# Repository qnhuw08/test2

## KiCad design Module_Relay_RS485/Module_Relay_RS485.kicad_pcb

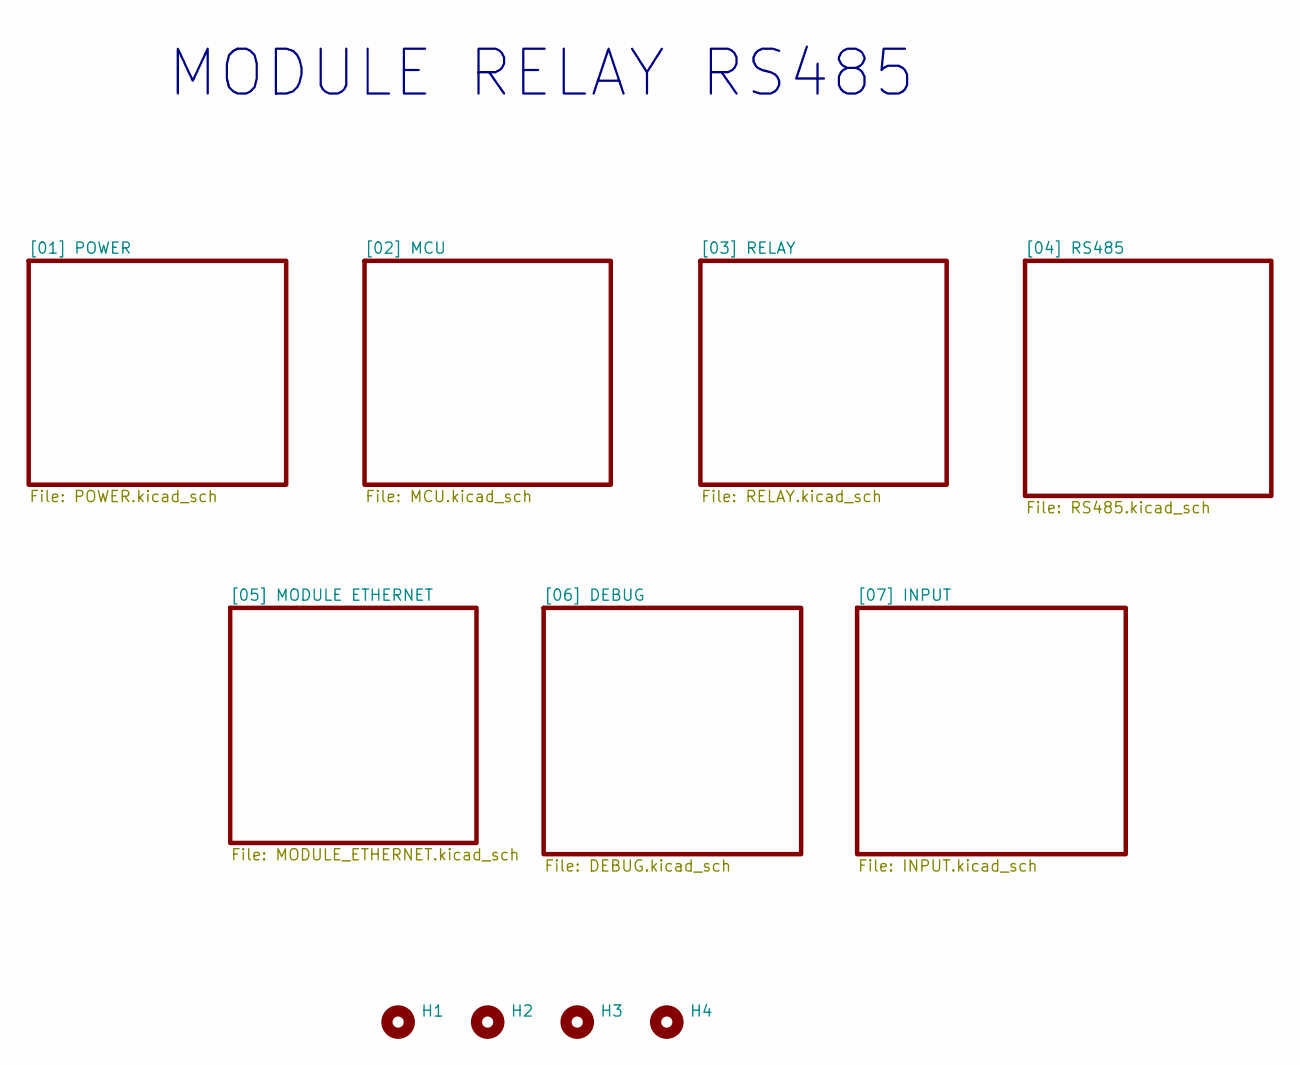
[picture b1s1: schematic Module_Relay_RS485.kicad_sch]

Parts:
H1, H2, H3, H4: MountingHole; MountingHole_3.2mm_M3_DIN965_Pad

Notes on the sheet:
MODULE RELAY RS485

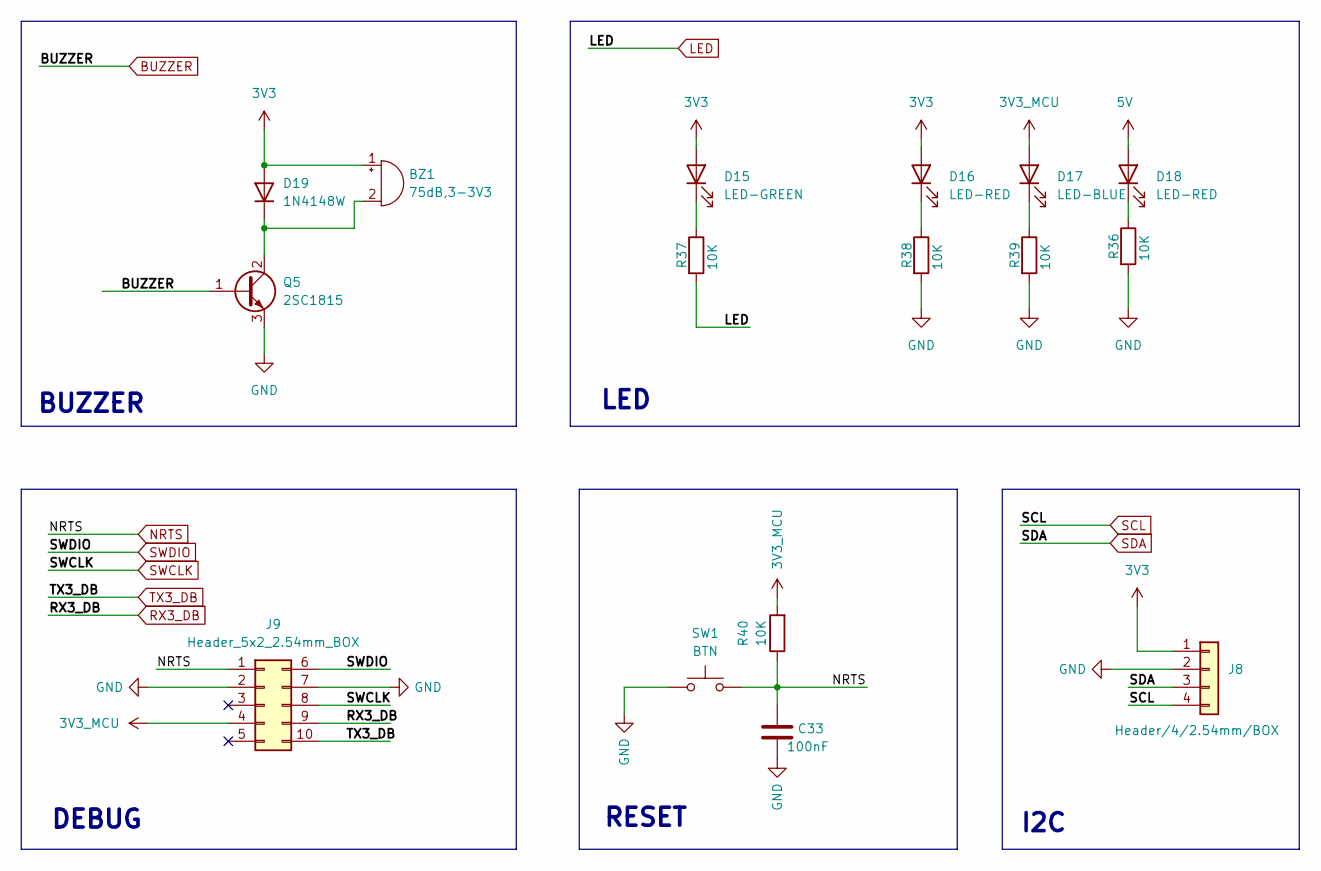
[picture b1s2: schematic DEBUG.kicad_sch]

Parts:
BZ1: 75dB,3-3V3; MagneticBuzzer_PUI_AT-0927-TT-6-R
C33: 100nF; C_0603_1608Metric
D15: LED-GREEN; LED_0805_2012Metric
D16, D18: LED-RED; LED_0805_2012Metric
D17: LED-BLUE; LED_0805_2012Metric
D19: 1N4148W; D_SOD-123
J8: Header/4/2.54mm/BOX; PinHeader_1x04_P2.54mm_Horizontal
J9: Header_5x2_2.54mm_BOX; Header_2x5_2.54mm_BOX
Q5: 2SC1815; SOT-23
R36, R37, R38, R39, R40: 10K; R_0603_1608Metric
SW1: BTN; SW_SPST_PTS645

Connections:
3V3: BZ1.1 (+), D15.2 (A), D16.2 (A), D19.2 (A), J8.1; also elsewhere on the board
3V3_MCU: D17.2 (A), J9.4, R40.2; also elsewhere on the board
5V: D18.2 (A); also elsewhere on the board
BUZZER: Q5.1 (B); also elsewhere on the board
GND: C33.2, J8.2, J9.2, J9.7, Q5.3 (E), R36.2, R38.2, R39.2, SW1.1; also elsewhere on the board
LED: R37.2; also elsewhere on the board
NRTS: C33.1, J9.1, R40.1, SW1.2; also elsewhere on the board
unnamed: BZ1.2 (-), D19.1 (K), Q5.2 (C)
unnamed: D15.1 (K), R37.1
unnamed: D16.1 (K), R38.1
unnamed: D17.1 (K), R39.1
unnamed: D18.1 (K), R36.1
RX3_DB: J9.9; also elsewhere on the board
SCL: J8.4; also elsewhere on the board
SDA: J8.3; also elsewhere on the board
SWCLK: J9.8; also elsewhere on the board
SWDIO: J9.6; also elsewhere on the board
TX3_DB: J9.10; also elsewhere on the board

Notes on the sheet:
I2C
LED
BUZZER
DEBUG
RESET

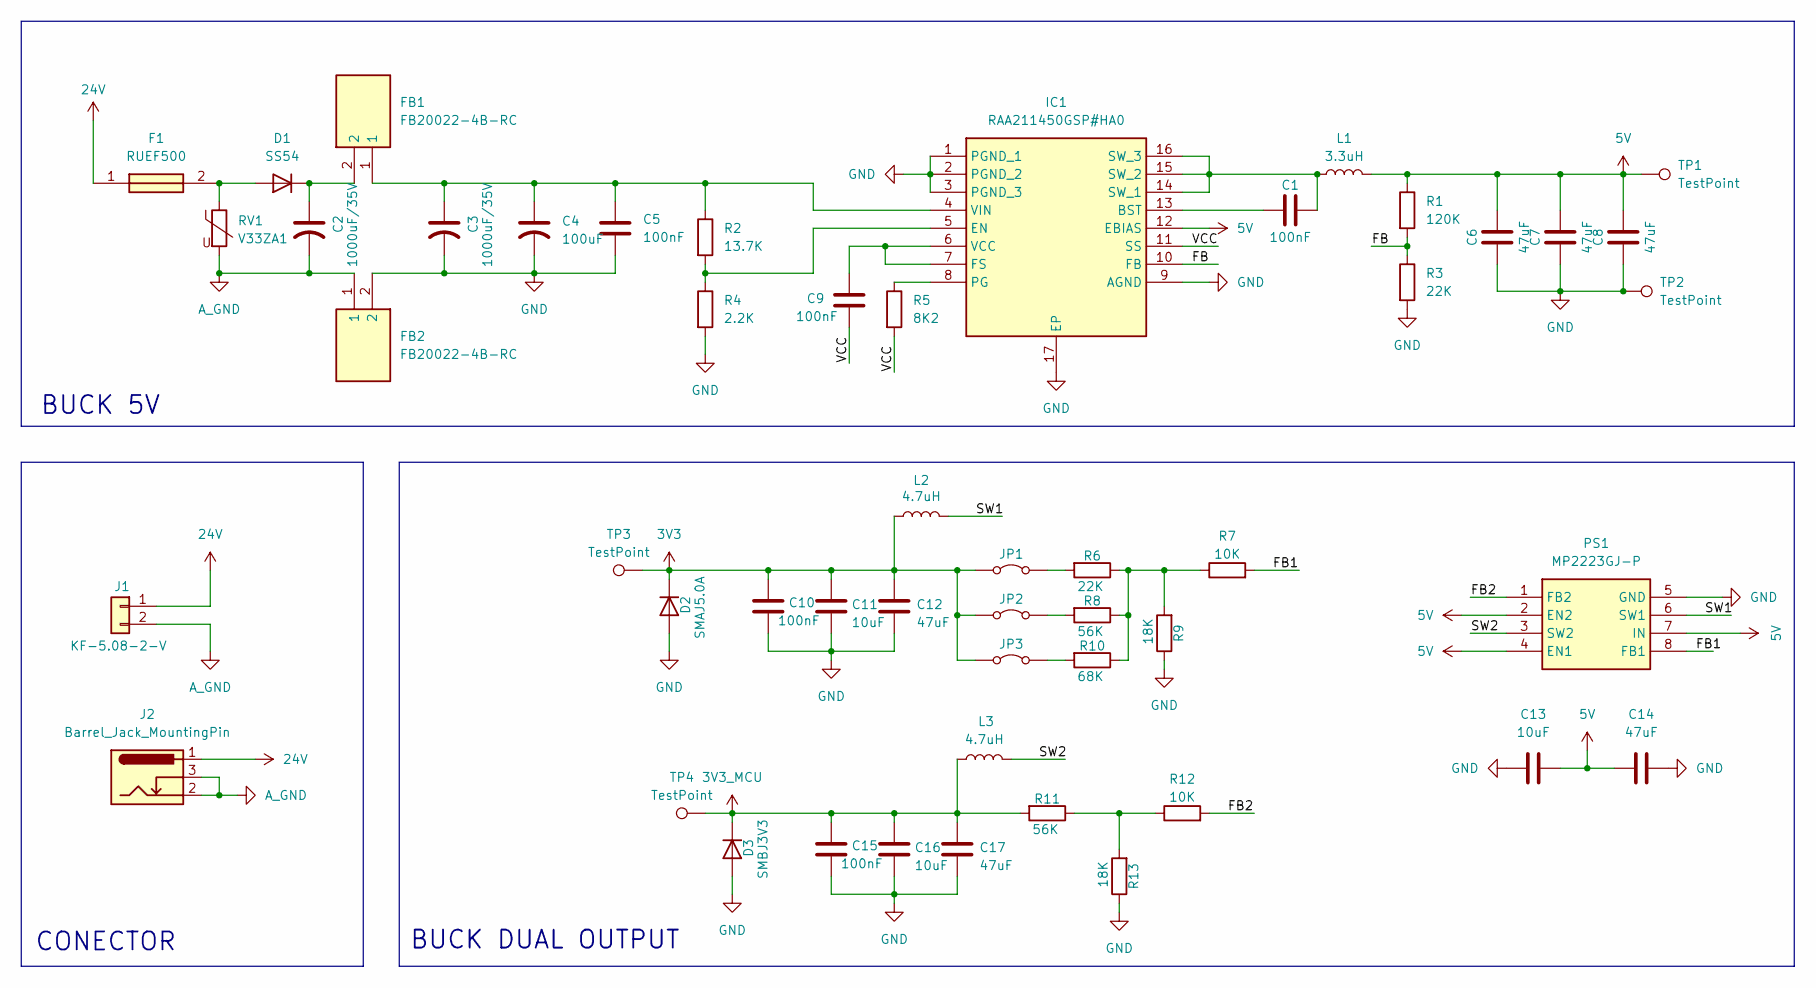
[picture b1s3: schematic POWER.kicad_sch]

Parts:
C1, C5, C9, C10, C15: 100nF; C_0603_1608Metric
C2, C3: 1000uF/35V; C_Radial_D10.0mm_H20.0mm_P5.00mm
C4: 100uF; CP_EIA-6032-15_Kemet-U_HandSolder
C6, C7, C8, C12, C14, C17: 47uF; C_1210_3225Metric
C11, C13, C16: 10uF; C_0805_2012Metric
D1: SS54; D_SMA
D2: SMAJ5.0A; D_SMA
D3: SMBJ3V3; D_SMB
F1: RUEF500; Manufacturer_Part_Number RUEF500
FB1, FB2: FB20022-4B-RC; FB200224BRC; Manufacturer_Part_Number FB20022-4B-RC; Mouser Part Number 542-FB20022-4B-RC
IC1: RAA211450GSP#HA0; SOP65P640X120-17N; Manufacturer_Part_Number RAA211450GSP#HA0; Mouser Part Number 968-RAA211450GSP#HA0
J1: KF-5.08-2-V; PhoenixContact_MSTBA_2,5_2-G-5,08_1x02_P5.08mm_Horizontal
J2: Barrel_Jack_MountingPin; BarrelJack_GCT_DCJ200-10-A_Horizontal
JP1, JP2, JP3: Jumper_2_Bridged; TestPoint_2Pads_Pitch2.54mm_Drill0.8mm
L1: 3.3uH; L_12x12mm_H8mm
L2, L3: 4.7uH; L_12x12mm_H8mm
PS1: MP2223GJ-P; SOT65P280X100-8N; Manufacturer_Part_Number MP2223GJ-P; Mouser Part Number 946-MP2223GJ-P
R1: 120K; R_0603_1608Metric
R2: 13.7K; R_0603_1608Metric
R3, R6: 22K; R_0603_1608Metric
R4: 2.2K; R_0603_1608Metric
R5: 8K2; R_0603_1608Metric
R7, R12: 10K; R_0603_1608Metric
R8, R11: 56K; R_0603_1608Metric
R9, R13: 18K; R_0603_1608Metric
R10: 68K; R_0603_1608Metric
RV1: V33ZA1; RV_Disc_D7mm_W3.6mm_P5mm
TP1, TP2, TP3, TP4: TestPoint; Pin_D1.3mm_L11.0mm

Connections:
3V3: C10.1, C11.1, C12.1, D2.1 (K), JP1.1 (A), JP2.1 (A), JP3.1 (A), L2.1, TP3.1; also elsewhere on the board
3V3_MCU: C15.1, C16.1, C17.1, D3.1 (K), L3.1, R11.2, TP4.1; also elsewhere on the board
5V: C6.2, C7.2, C8.2, C13.2, C14.1, IC1.12 (EBIAS), L1.2, PS1.2 (EN2), PS1.4 (EN1), PS1.7 (IN), R1.1, TP1.1; also elsewhere on the board
24V: F1.1, J1.1, J2.1
/[01] POWER/FB1: PS1.8 (FB1), R7.2
/[01] POWER/FB2: PS1.1 (FB2), R12.2
/[01] POWER/FB: IC1.10 (FB), R1.2, R3.1
/[01] POWER/SW1: L2.2, PS1.6 (SW1)
/[01] POWER/SW2: L3.2, PS1.3 (SW2)
/[01] POWER/VCC: C9.2, IC1.11 (SS), R5.2
A_GND: C2.2, FB2.1, J1.2, J2.2, J2.3, RV1.2
GND: C3.2, C4.2, C5.2, C6.1, C7.1, C8.1, C10.2, C11.2, C12.2, C13.1, C14.2, C15.2, C16.2, C17.2, D2.2 (A), D3.2 (A), FB2.2, IC1.1 (PGND_1), IC1.2 (PGND_2), IC1.3 (PGND_3), IC1.9 (AGND), IC1.17 (EP), PS1.5 (GND), R3.2, R4.2, R9.1, R13.1, TP2.1; also elsewhere on the board
unnamed: D1.2 (A), F1.2, RV1.1
unnamed: C2.1, D1.1 (K), FB1.2
unnamed: C1.1, IC1.13 (BST)
unnamed: IC1.5 (EN), R2.2, R4.1
unnamed: C9.1, IC1.6 (VCC), IC1.7 (FS)
unnamed: IC1.8 (PG), R5.1
unnamed: C1.2, IC1.14 (SW_1), IC1.15 (SW_2), IC1.16 (SW_3), L1.1
unnamed: C3.1, C4.1, C5.1, FB1.1, IC1.4 (VIN), R2.1
unnamed: JP1.2 (B), R6.2
unnamed: JP2.2 (B), R8.2
unnamed: JP3.2 (B), R10.2
unnamed: R6.1, R7.1, R8.1, R9.2, R10.1
unnamed: R11.1, R12.1, R13.2

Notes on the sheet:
BUCK 5V
CONECTOR
BUCK DUAL OUTPUT

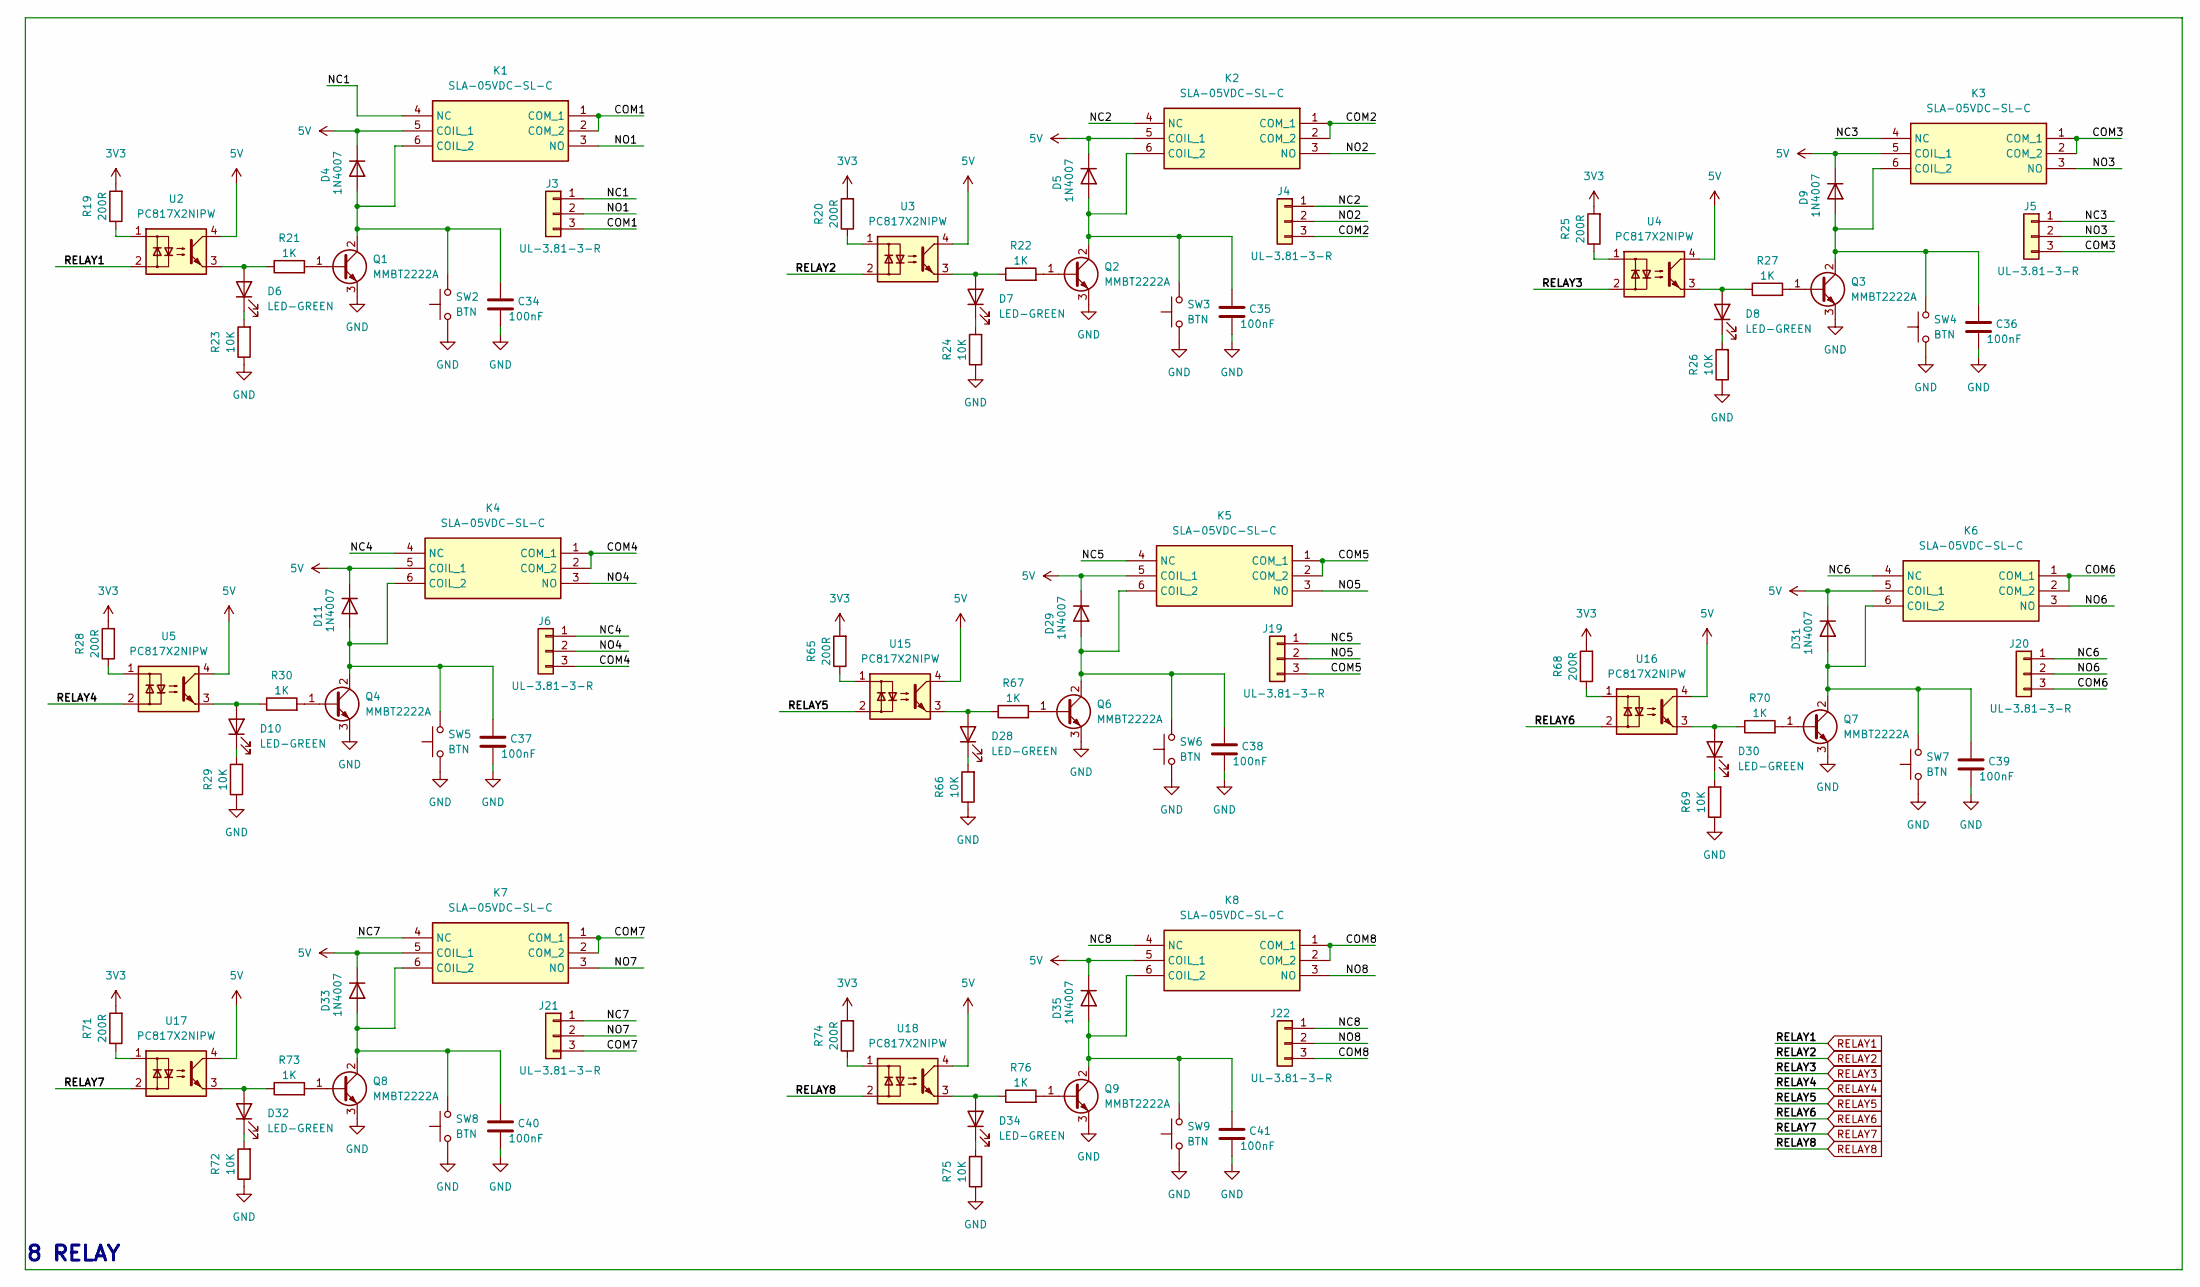
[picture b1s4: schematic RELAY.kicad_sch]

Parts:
C34, C35, C36, C37, C38, C39, C40, C41: 100nF; C_0603_1608Metric
D4, D5, D9, D11, D29, D31, D33, D35: 1N4007; D_SMA
D6, D7, D8, D10, D28, D30, D32, D34: LED-GREEN; LED_0805_2012Metric
J3, J4, J5, J6, J19, J20, J21, J22: UL-3.81-3-R; PhoenixContact_MC_1,5_3-G-3.81_1x03_P3.81mm_Horizontal
K1, K2, K3, K4, K5, K6, K7, K8: SLA-05VDC-SL-C; SLA05VDCSLC; Manufacturer_Part_Number SLA-05VDC-SL-C
Q1, Q2, Q3, Q4, Q6, Q7, Q8, Q9: MMBT2222A; SOT-23
R19, R20, R25, R28, R65, R68, R71, R74: 200R; R_0603_1608Metric
R21, R22, R27, R30, R67, R70, R73, R76: 1K; R_0603_1608Metric
R23, R24, R26, R29, R66, R69, R72, R75: 10K; R_0603_1608Metric
SW2, SW3, SW4, SW5, SW6, SW7, SW8, SW9: BTN; SW_SPST_PTS645
U2, U3, U4, U5, U15, U16, U17, U18: PC817X2NIPW; SOP254P960X380-4N

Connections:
3V3: R19.2, R20.2, R25.2, R28.2, R65.2, R68.2, R71.2, R74.2; also elsewhere on the board
5V: D4.1 (K), D5.1 (K), D9.1 (K), D11.1 (K), D29.1 (K), D31.1 (K), D33.1 (K), D35.1 (K), K1.5 (COIL_1), K2.5 (COIL_1), K3.5 (COIL_1), K4.5 (COIL_1), K5.5 (COIL_1), K6.5 (COIL_1), K7.5 (COIL_1), K8.5 (COIL_1), U2.4, U3.4, U4.4, U5.4, U15.4, U16.4, U17.4, U18.4; also elsewhere on the board
/[03] RELAY/COM1: J3.3, K1.1 (COM_1), K1.2 (COM_2)
/[03] RELAY/COM2: J4.3, K2.1 (COM_1), K2.2 (COM_2)
/[03] RELAY/COM3: J5.3, K3.1 (COM_1), K3.2 (COM_2)
/[03] RELAY/COM4: J6.3, K4.1 (COM_1), K4.2 (COM_2)
/[03] RELAY/COM5: J19.3, K5.1 (COM_1), K5.2 (COM_2)
/[03] RELAY/COM6: J20.3, K6.1 (COM_1), K6.2 (COM_2)
/[03] RELAY/COM7: J21.3, K7.1 (COM_1), K7.2 (COM_2)
/[03] RELAY/COM8: J22.3, K8.1 (COM_1), K8.2 (COM_2)
/[03] RELAY/NC1: J3.1, K1.4 (NC)
/[03] RELAY/NC2: J4.1, K2.4 (NC)
/[03] RELAY/NC3: J5.1, K3.4 (NC)
/[03] RELAY/NC4: J6.1, K4.4 (NC)
/[03] RELAY/NC5: J19.1, K5.4 (NC)
/[03] RELAY/NC6: J20.1, K6.4 (NC)
/[03] RELAY/NC7: J21.1, K7.4 (NC)
/[03] RELAY/NC8: J22.1, K8.4 (NC)
/[03] RELAY/NO1: J3.2, K1.3 (NO)
/[03] RELAY/NO2: J4.2, K2.3 (NO)
/[03] RELAY/NO3: J5.2, K3.3 (NO)
/[03] RELAY/NO4: J6.2, K4.3 (NO)
/[03] RELAY/NO5: J19.2, K5.3 (NO)
/[03] RELAY/NO6: J20.2, K6.3 (NO)
/[03] RELAY/NO7: J21.2, K7.3 (NO)
/[03] RELAY/NO8: J22.2, K8.3 (NO)
GND: C34.2, C35.2, C36.2, C37.2, C38.2, C39.2, C40.2, C41.2, Q1.3 (E), Q2.3 (E), Q3.3 (E), Q4.3 (E), Q6.3 (E), Q7.3 (E), Q8.3 (E), Q9.3 (E), R23.1, R24.1, R26.1, R29.1, R66.1, R69.1, R72.1, R75.1, SW2.1, SW3.1, SW4.1, SW5.1, SW6.1, SW7.1, SW8.1, SW9.1; also elsewhere on the board
unnamed: C34.1, D4.2 (A), K1.6 (COIL_2), Q1.2 (C), SW2.2
unnamed: C35.1, D5.2 (A), K2.6 (COIL_2), Q2.2 (C), SW3.2
unnamed: D6.2 (A), R21.1, U2.3
unnamed: D6.1 (K), R23.2
unnamed: D7.2 (A), R22.1, U3.3
unnamed: D7.1 (K), R24.2
unnamed: D8.2 (A), R27.1, U4.3
unnamed: D8.1 (K), R26.2
unnamed: C36.1, D9.2 (A), K3.6 (COIL_2), Q3.2 (C), SW4.2
unnamed: D10.2 (A), R30.1, U5.3
unnamed: D10.1 (K), R29.2
unnamed: C37.1, D11.2 (A), K4.6 (COIL_2), Q4.2 (C), SW5.2
unnamed: D28.2 (A), R67.1, U15.3
unnamed: D28.1 (K), R66.2
unnamed: C38.1, D29.2 (A), K5.6 (COIL_2), Q6.2 (C), SW6.2
unnamed: D30.2 (A), R70.1, U16.3
unnamed: D30.1 (K), R69.2
unnamed: C39.1, D31.2 (A), K6.6 (COIL_2), Q7.2 (C), SW7.2
unnamed: D32.2 (A), R73.1, U17.3
unnamed: D32.1 (K), R72.2
unnamed: C40.1, D33.2 (A), K7.6 (COIL_2), Q8.2 (C), SW8.2
unnamed: D34.2 (A), R76.1, U18.3
unnamed: D34.1 (K), R75.2
unnamed: C41.1, D35.2 (A), K8.6 (COIL_2), Q9.2 (C), SW9.2
unnamed: Q1.1 (B), R21.2
unnamed: Q2.1 (B), R22.2
unnamed: Q3.1 (B), R27.2
unnamed: Q4.1 (B), R30.2
unnamed: Q6.1 (B), R67.2
unnamed: Q7.1 (B), R70.2
unnamed: Q8.1 (B), R73.2
unnamed: Q9.1 (B), R76.2
unnamed: R19.1, U2.1
unnamed: R20.1, U3.1
unnamed: R25.1, U4.1
unnamed: R28.1, U5.1
unnamed: R65.1, U15.1
unnamed: R68.1, U16.1
unnamed: R71.1, U17.1
unnamed: R74.1, U18.1
RELAY1: U2.2; also elsewhere on the board
RELAY2: U3.2; also elsewhere on the board
RELAY3: U4.2; also elsewhere on the board
RELAY4: U5.2; also elsewhere on the board
RELAY5: U15.2; also elsewhere on the board
RELAY6: U16.2; also elsewhere on the board
RELAY7: U17.2; also elsewhere on the board
RELAY8: U18.2; also elsewhere on the board

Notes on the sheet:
8 RELAY

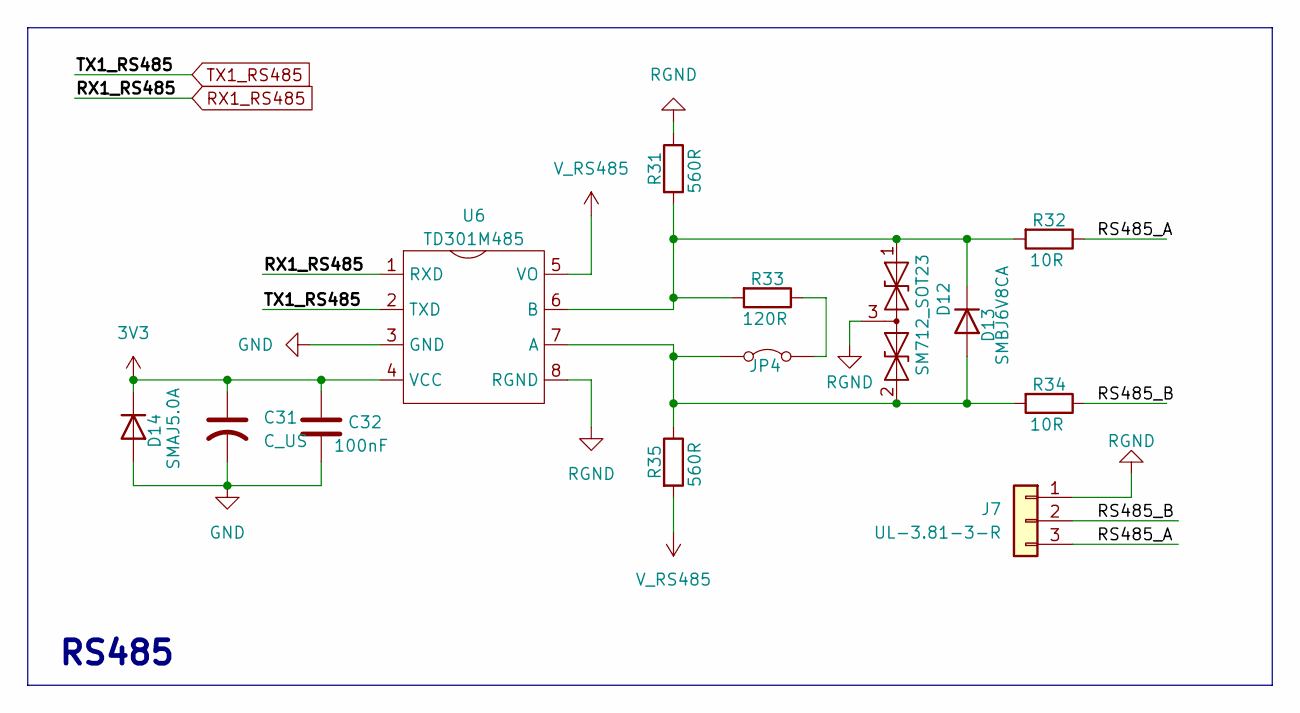
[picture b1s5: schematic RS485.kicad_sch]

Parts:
C31: C_US; C_1206_3216Metric
C32: 100nF; C_0603_1608Metric
D12: SM712_SOT23; SOT-23
D13: SMBJ6V8CA; D_SMA
D14: SMAJ5.0A; D_SMA
J7: UL-3.81-3-R; PhoenixContact_MC_1,5_3-G-3.81_1x03_P3.81mm_Horizontal
JP4: Jumper_2_Bridged; SW_DIP_SPSTx01_Slide_9.78x4.72mm_W7.62mm_P2.54mm
R31, R35: 560R; R_0603_1608Metric
R32, R34: 10R; R_1210_3225Metric
R33: 120R; R_0603_1608Metric
U6: TD301M485

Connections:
3V3: C31.1, C32.1, D14.1 (K), U6.4 (VCC); also elsewhere on the board
/[04] RS485/RS485_A: J7.3, R32.1
/[04] RS485/RS485_B: J7.2, R34.1
GND: C31.2, C32.2, D14.2 (A), U6.3 (GND); also elsewhere on the board
unnamed: D12.1 (A1), D13.1 (K), R31.2, R32.2, R33.2, U6.6 (B)
unnamed: D12.2 (A2), D13.2 (A), JP4.1 (A), R34.2, R35.1, U6.7 (A)
unnamed: JP4.2 (B), R33.1
RGND: D12.3 (common), J7.1, R31.1, U6.8 (RGND)
RX1_RS485: U6.1 (RXD); also elsewhere on the board
TX1_RS485: U6.2 (TXD); also elsewhere on the board
V_RS485: R35.2, U6.5 (VO)

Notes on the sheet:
RS485

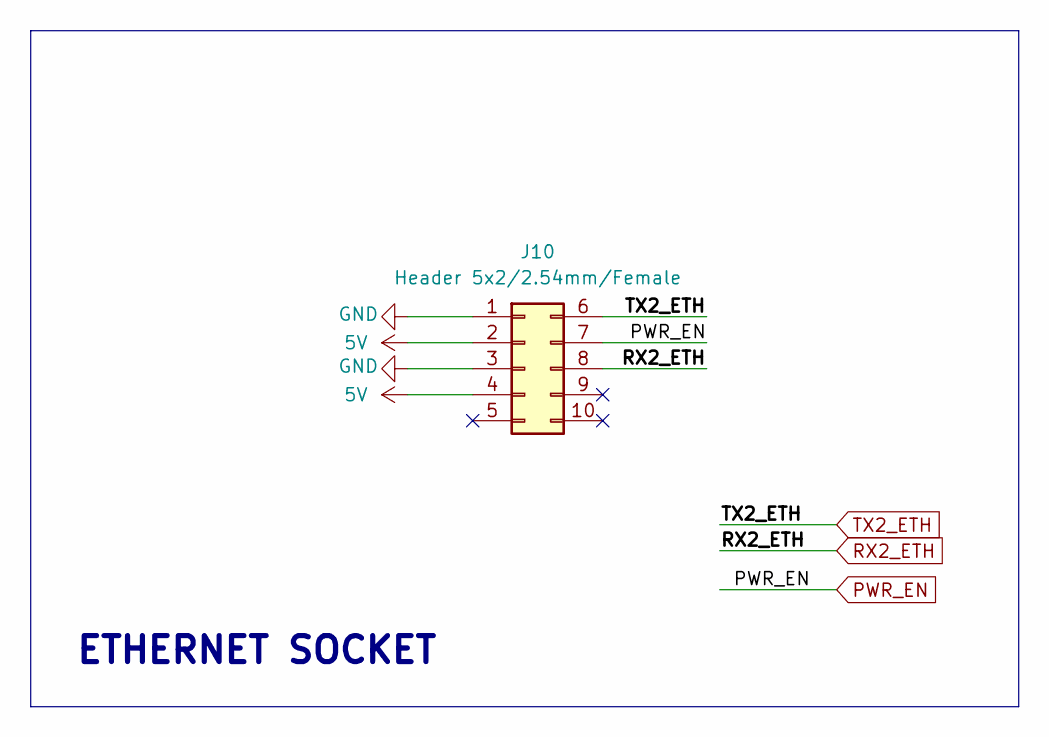
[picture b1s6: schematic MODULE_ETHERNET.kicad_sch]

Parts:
J10: Header 5x2/2.54mm/Female; PinSocket_2x05_P2.54mm_Vertical

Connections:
5V: J10.2, J10.4; also elsewhere on the board
GND: J10.1, J10.3; also elsewhere on the board
PWR_EN: J10.7; also elsewhere on the board
RX2_ETH: J10.8; also elsewhere on the board
TX2_ETH: J10.6; also elsewhere on the board

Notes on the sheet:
ETHERNET SOCKET

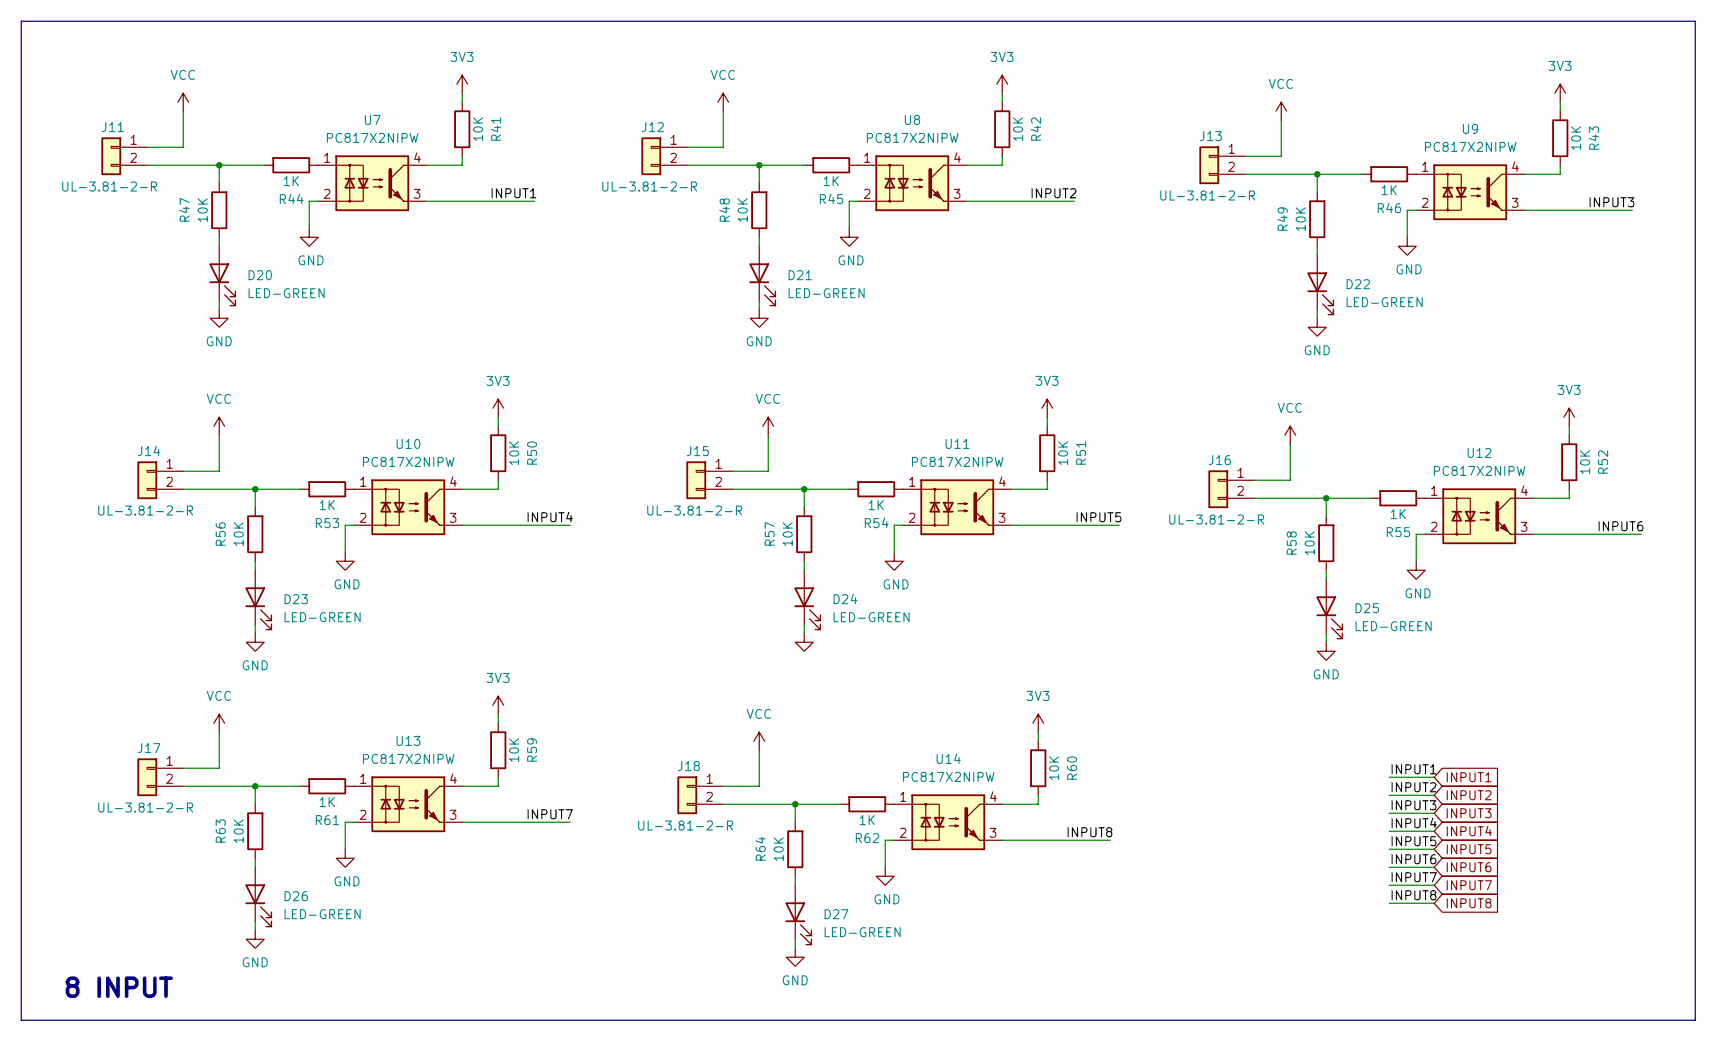
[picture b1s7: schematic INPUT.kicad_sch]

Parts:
D20, D21, D22, D23, D24, D25, D26, D27: LED-GREEN; LED_0805_2012Metric
J11, J12, J13, J14, J15, J16, J17, J18: UL-3.81-2-R; PhoenixContact_MC_1,5_2-G-3.81_1x02_P3.81mm_Horizontal
R41, R42, R43, R47, R48, R49, R50, R51, R52, R56, R57, R58, R59, R60, R63, R64: 10K; R_0603_1608Metric
R44, R45, R46, R53, R54, R55, R61, R62: 1K; R_0603_1608Metric
U7, U8, U9, U10, U11, U12, U13, U14: PC817X2NIPW; SOP254P960X380-4N

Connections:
3V3: R41.1, R42.1, R43.1, R50.1, R51.1, R52.1, R59.1, R60.1; also elsewhere on the board
GND: D20.1 (K), D21.1 (K), D22.1 (K), D23.1 (K), D24.1 (K), D25.1 (K), D26.1 (K), D27.1 (K), U7.2, U8.2, U9.2, U10.2, U11.2, U12.2, U13.2, U14.2; also elsewhere on the board
INPUT1: U7.3; also elsewhere on the board
INPUT2: U8.3; also elsewhere on the board
INPUT3: U9.3; also elsewhere on the board
INPUT4: U10.3; also elsewhere on the board
INPUT5: U11.3; also elsewhere on the board
INPUT6: U12.3; also elsewhere on the board
INPUT7: U13.3; also elsewhere on the board
INPUT8: U14.3; also elsewhere on the board
unnamed: D20.2 (A), R47.1
unnamed: D21.2 (A), R48.1
unnamed: D22.2 (A), R49.1
unnamed: D23.2 (A), R56.1
unnamed: D24.2 (A), R57.1
unnamed: D25.2 (A), R58.1
unnamed: D26.2 (A), R63.1
unnamed: D27.2 (A), R64.1
unnamed: J11.2, R44.2, R47.2
unnamed: J12.2, R45.2, R48.2
unnamed: J13.2, R46.2, R49.2
unnamed: J14.2, R53.2, R56.2
unnamed: J15.2, R54.2, R57.2
unnamed: J16.2, R55.2, R58.2
unnamed: J17.2, R61.2, R63.2
unnamed: J18.2, R62.2, R64.2
unnamed: R41.2, U7.4
unnamed: R42.2, U8.4
unnamed: R43.2, U9.4
unnamed: R44.1, U7.1
unnamed: R45.1, U8.1
unnamed: R46.1, U9.1
unnamed: R50.2, U10.4
unnamed: R51.2, U11.4
unnamed: R52.2, U12.4
unnamed: R53.1, U10.1
unnamed: R54.1, U11.1
unnamed: R55.1, U12.1
unnamed: R59.2, U13.4
unnamed: R60.2, U14.4
unnamed: R61.1, U13.1
unnamed: R62.1, U14.1
VCC: J11.1, J12.1, J13.1, J14.1, J15.1, J16.1, J17.1, J18.1

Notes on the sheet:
8 INPUT

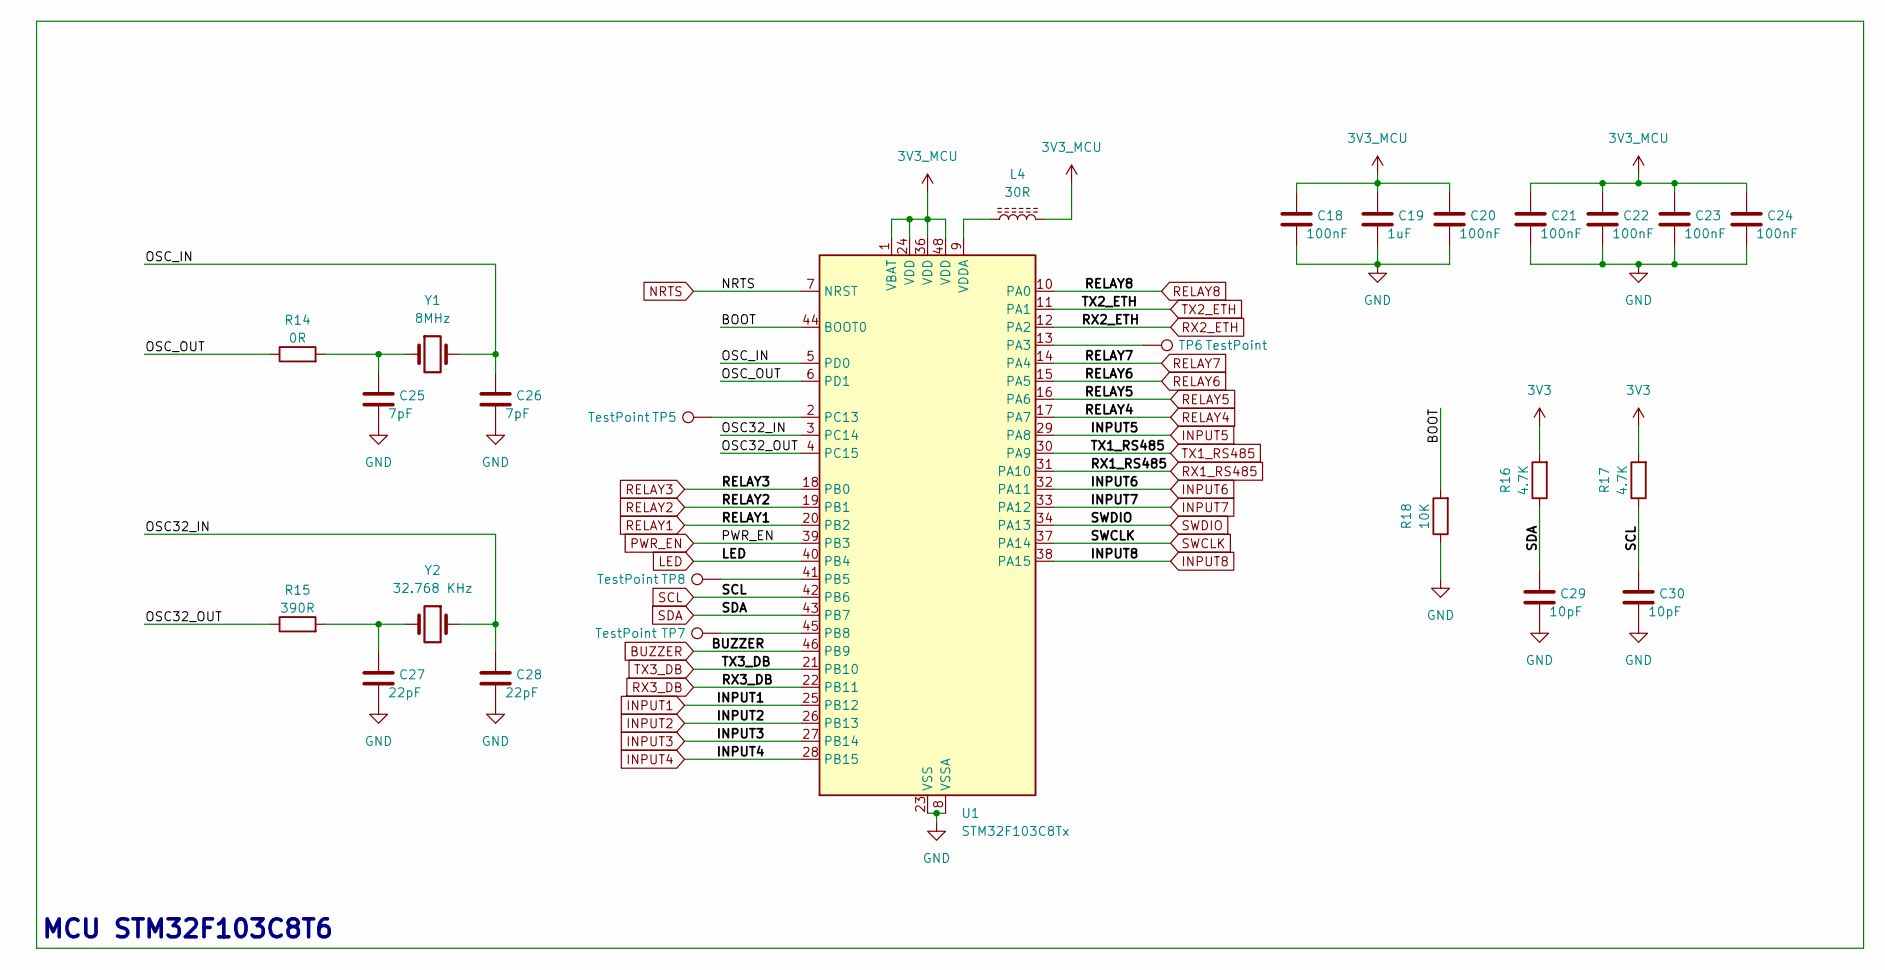
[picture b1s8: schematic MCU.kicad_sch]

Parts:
C18, C20, C21, C22, C23, C24: 100nF; C_0603_1608Metric
C19: 1uF; C_0603_1608Metric
C25, C26: 7pF; C_0603_1608Metric
C27, C28: 22pF; C_0603_1608Metric
C29, C30: 10pF; C_0603_1608Metric
L4: 30R; L_0805_2012Metric
R14: 0R; R_0603_1608Metric
R15: 390R; R_0603_1608Metric
R16, R17: 4.7K; R_0603_1608Metric
R18: 10K; R_0603_1608Metric
TP5, TP6, TP7, TP8: TestPoint; Pin_D1.3mm_L11.0mm
U1: STM32F103C8Tx; LQFP-48_7x7mm_P0.5mm
Y1: 8MHz; Crystal_HC49-4H_Vertical
Y2: 32.768 KHz; Crystal_C38-LF_D3.0mm_L8.0mm_Horizontal

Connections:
3V3: R16.2, R17.2; also elsewhere on the board
3V3_MCU: C18.1, C19.1, C20.1, C21.1, C22.1, C23.1, C24.1, L4.2, U1.1 (VBAT), U1.24 (VDD), U1.36 (VDD), U1.48 (VDD); also elsewhere on the board
/[02] MCU/BOOT: R18.2, U1.44 (BOOT0)
/[02] MCU/OSC32_IN: C28.1, U1.3 (PC14), Y2.1
/[02] MCU/OSC32_OUT: R15.1, U1.4 (PC15)
/[02] MCU/OSC_IN: C26.1, U1.5 (PD0), Y1.2
/[02] MCU/OSC_OUT: R14.1, U1.6 (PD1)
BUZZER: U1.46 (PB9); also elsewhere on the board
GND: C18.2, C19.2, C20.2, C21.2, C22.2, C23.2, C24.2, C25.2, C26.2, C27.2, C28.2, C29.2, C30.2, R18.1, U1.8 (VSSA), U1.23 (VSS), U1.35 (VSS), U1.47 (VSS); also elsewhere on the board
INPUT1: U1.25 (PB12); also elsewhere on the board
INPUT2: U1.26 (PB13); also elsewhere on the board
INPUT3: U1.27 (PB14); also elsewhere on the board
INPUT4: U1.28 (PB15); also elsewhere on the board
INPUT5: U1.29 (PA8); also elsewhere on the board
INPUT6: U1.32 (PA11); also elsewhere on the board
INPUT7: U1.33 (PA12); also elsewhere on the board
INPUT8: U1.38 (PA15); also elsewhere on the board
LED: U1.40 (PB4); also elsewhere on the board
NRTS: U1.7 (NRST); also elsewhere on the board
unnamed: C25.1, R14.2, Y1.1
unnamed: C27.1, R15.2, Y2.2
unnamed: TP6.1, U1.13 (PA3)
unnamed: TP8.1, U1.41 (PB5)
unnamed: TP7.1, U1.45 (PB8)
unnamed: TP5.1, U1.2 (PC13)
unnamed: L4.1, U1.9 (VDDA)
PWR_EN: U1.39 (PB3); also elsewhere on the board
RELAY1: U1.20 (PB2); also elsewhere on the board
RELAY2: U1.19 (PB1); also elsewhere on the board
RELAY3: U1.18 (PB0); also elsewhere on the board
RELAY4: U1.17 (PA7); also elsewhere on the board
RELAY5: U1.16 (PA6); also elsewhere on the board
RELAY6: U1.15 (PA5); also elsewhere on the board
RELAY7: U1.14 (PA4); also elsewhere on the board
RELAY8: U1.10 (PA0); also elsewhere on the board
RX1_RS485: U1.31 (PA10); also elsewhere on the board
RX2_ETH: U1.12 (PA2); also elsewhere on the board
RX3_DB: U1.22 (PB11); also elsewhere on the board
SCL: C30.1, R17.1, U1.42 (PB6); also elsewhere on the board
SDA: C29.1, R16.1, U1.43 (PB7); also elsewhere on the board
SWCLK: U1.37 (PA14); also elsewhere on the board
SWDIO: U1.34 (PA13); also elsewhere on the board
TX1_RS485: U1.30 (PA9); also elsewhere on the board
TX2_ETH: U1.11 (PA1); also elsewhere on the board
TX3_DB: U1.21 (PB10); also elsewhere on the board

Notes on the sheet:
MCU STM32F103C8T6

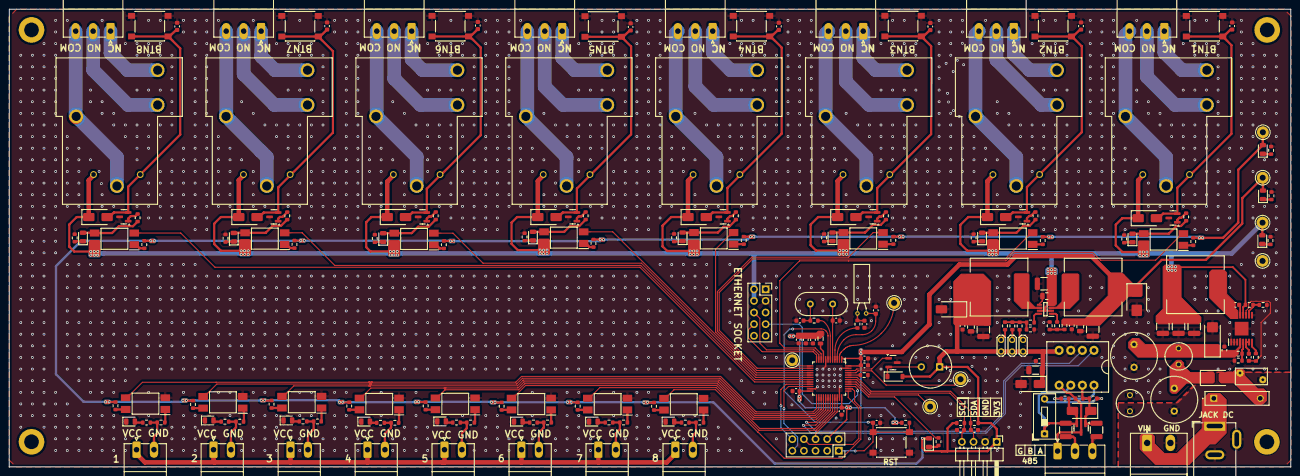
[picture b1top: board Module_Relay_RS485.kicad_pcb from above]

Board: 2 copper layers, 280.0 x 100.0 mm, 247 parts (0 on the bottom side), 176 nets.

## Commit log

2026-03-02 fisrt up load HW
